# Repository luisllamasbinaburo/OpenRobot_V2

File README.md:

# OpenRobot v2

OpenRobot v2 is an Open Hardware PCB based on Arduino Nano, especially designed for teaching technology

Once assembled, you can use make multiple projects and robots without welding, just adding or removing components in the dupont headers.

OpenRobot v2 is based on a modular design. Just select your main MCU module (Arduino Nano, ESP32, M5Stack...), and the module your project needs (Motors, GPIOs expansion...). Check the Wiki for information about each module.

## What can I make with OpenRobot v2?
Almost any DIY project you can ever imagine! 

Some of them,
- DC Motors Robot, like obstacle avoider (ultrasonic or Sharp), line follower, self-balancing bot...
- Servo Motor Robot, like 2-DOF Tower, 6-DOF Arms...
- Mosfet output for high current proyects (LED, electromagnets, water pumps)
- Bluetooth projects (HC-05/HC-06), like Android or PC communication, beacons...
- WiFi projects (ESP01), like controlling from Web, MQTT datalogger...
- Temperature, pressure, humidity weather station with BME280
- Any other project, thanks to the multiple available outputs!

## Modules
More info about each module in Wiki

#### PowerSource
- DC Converter ([Wiki link](https://github.com/luisllamasbinaburo/OpenRobot_V2/wiki/Module_PowerSource))

#### MCUs
- Arduino Nano ([Wiki link](https://github.com/luisllamasbinaburo/OpenRobot_V2/wiki/Module_MCU_ArduinoNano))
- ESP32 Embed ([Wiki link](https://github.com/luisllamasbinaburo/OpenRobot_V2/wiki/Module_MCU_ESP32Embed))
- M5StickC / M5Stack Atom ([Wiki link](https://github.com/luisllamasbinaburo/OpenRobot_V2/wiki/Module_MCU_M5Stack))

#### Motors
- DC Motors ([Wiki link](https://github.com/luisllamasbinaburo/OpenRobot_V2/wiki/Module_Motor_DC))
- Steppers ([Wiki link](https://github.com/luisllamasbinaburo/OpenRobot_V2/wiki/Module_Motor_Stepper))
- I2C Servos ([Wiki link](https://github.com/luisllamasbinaburo/OpenRobot_V2/wiki/Module_I2C_Servo))

#### Expansions
- I2C GPIO ([Wiki link](https://github.com/luisllamasbinaburo/OpenRobot_V2/wiki/Module_I2C_GPIO))
- I2C TOF ([Wiki link](https://github.com/luisllamasbinaburo/OpenRobot_V2/wiki/Module_I2C_TOF))
- Mosfet ([Wiki link](https://github.com/luisllamasbinaburo/OpenRobot_V2/wiki/Module_Expansion_Mosfet))

## TODO:
- Improve documentation
- Improve code source / utilities (libraries, examples...)

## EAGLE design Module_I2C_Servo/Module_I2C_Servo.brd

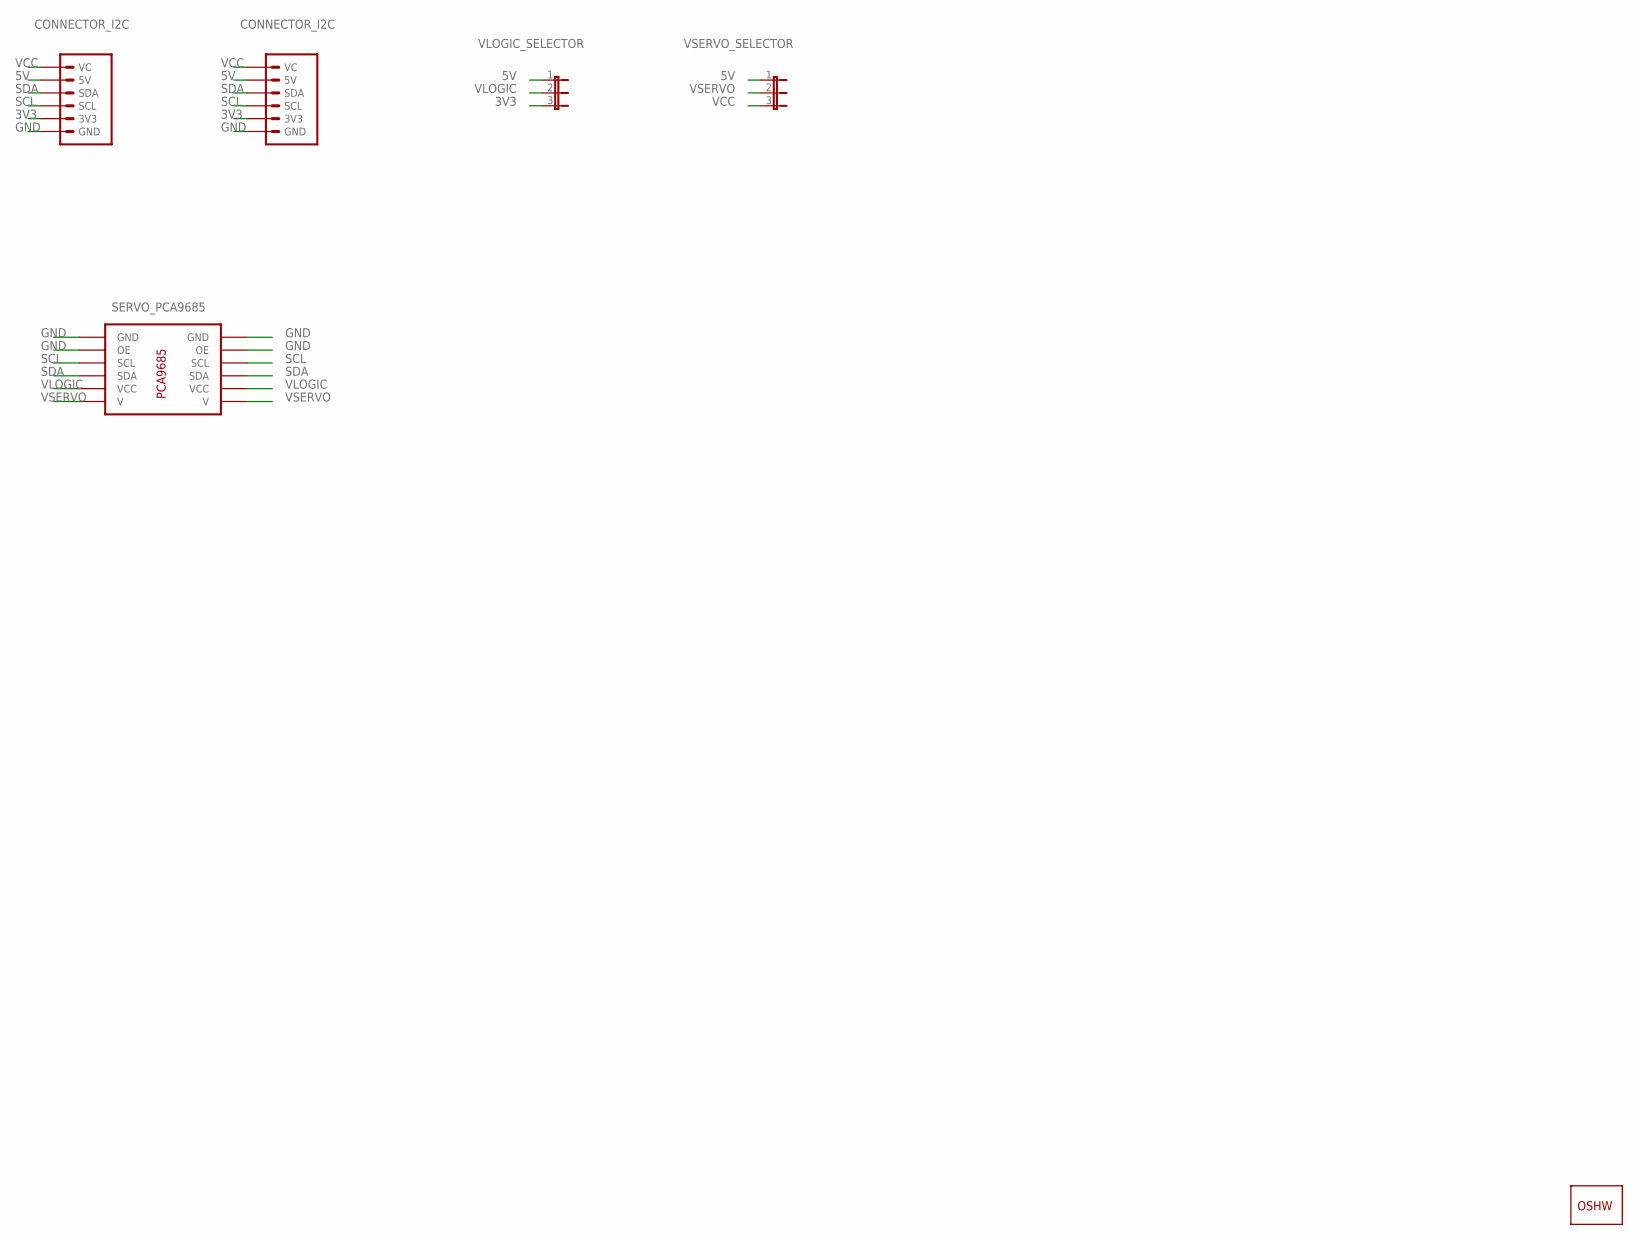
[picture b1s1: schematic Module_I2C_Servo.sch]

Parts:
GOLD_ORB_SM1: OSHWLOGO_GOLD_ORB_MED; OSHW1
U$2: SERVO_PCA9685
U$3, U$4: CONNECTOR_I2C
VLOGIC_SELECTOR: JUMPER_3
VSERVO_SELECTOR: JUMPER_3

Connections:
3V3: U$3.3V3, U$4.3V3, VLOGIC_SELECTOR.3
5V: U$3.5V, U$4.5V, VLOGIC_SELECTOR.1, VSERVO_SELECTOR.1
GND: U$2.GND@0 (GND), U$2.GND@1 (GND), U$2.OE@0 (OE), U$2.OE@1 (OE), U$3.GND, U$4.GND
SCL: U$2.SCL@0 (SCL), U$2.SCL@1 (SCL), U$3.SCL, U$4.SCL
SDA: U$2.SDA@0 (SDA), U$2.SDA@1 (SDA), U$3.SDA, U$4.SDA
VCC: U$3.VC, U$4.VC, VSERVO_SELECTOR.3
VLOGIC: U$2.VCC@0 (VCC), U$2.VCC@1 (VCC), VLOGIC_SELECTOR.2
VSERVO: U$2.VSERVO@0 (V), U$2.VSERVO@1 (V), VSERVO_SELECTOR.2

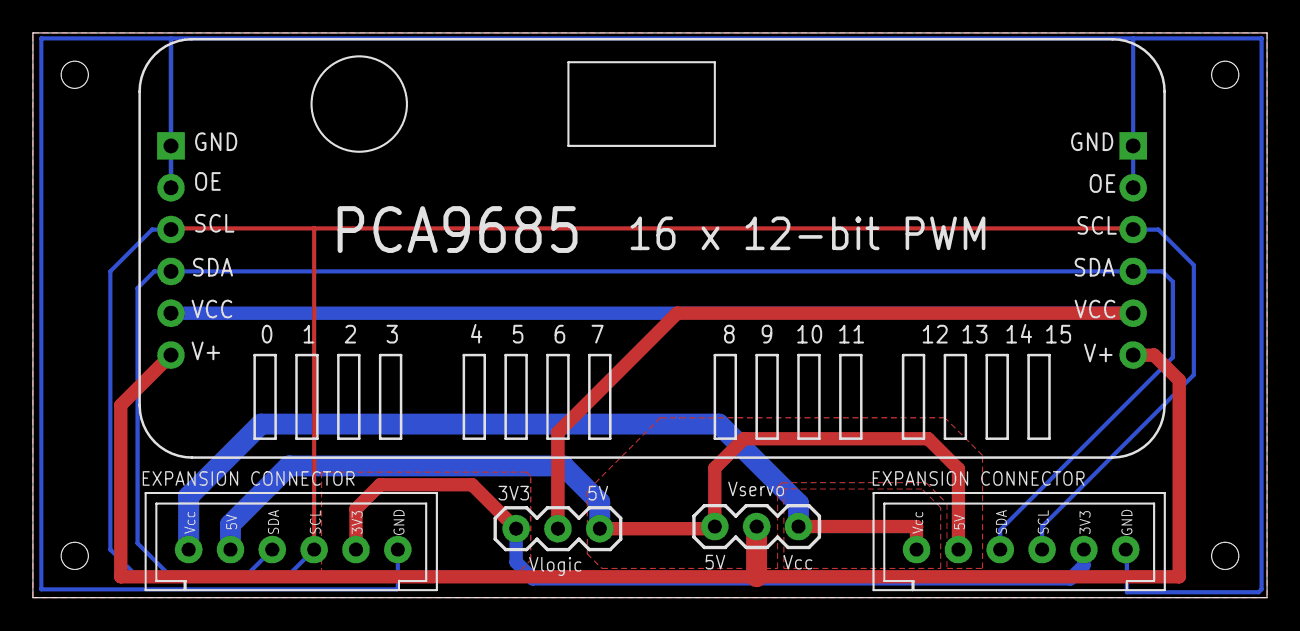
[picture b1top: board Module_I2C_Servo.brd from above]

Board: 2 copper layers, 74.9 x 34.3 mm, 6 parts (1 on the bottom side), 8 nets.

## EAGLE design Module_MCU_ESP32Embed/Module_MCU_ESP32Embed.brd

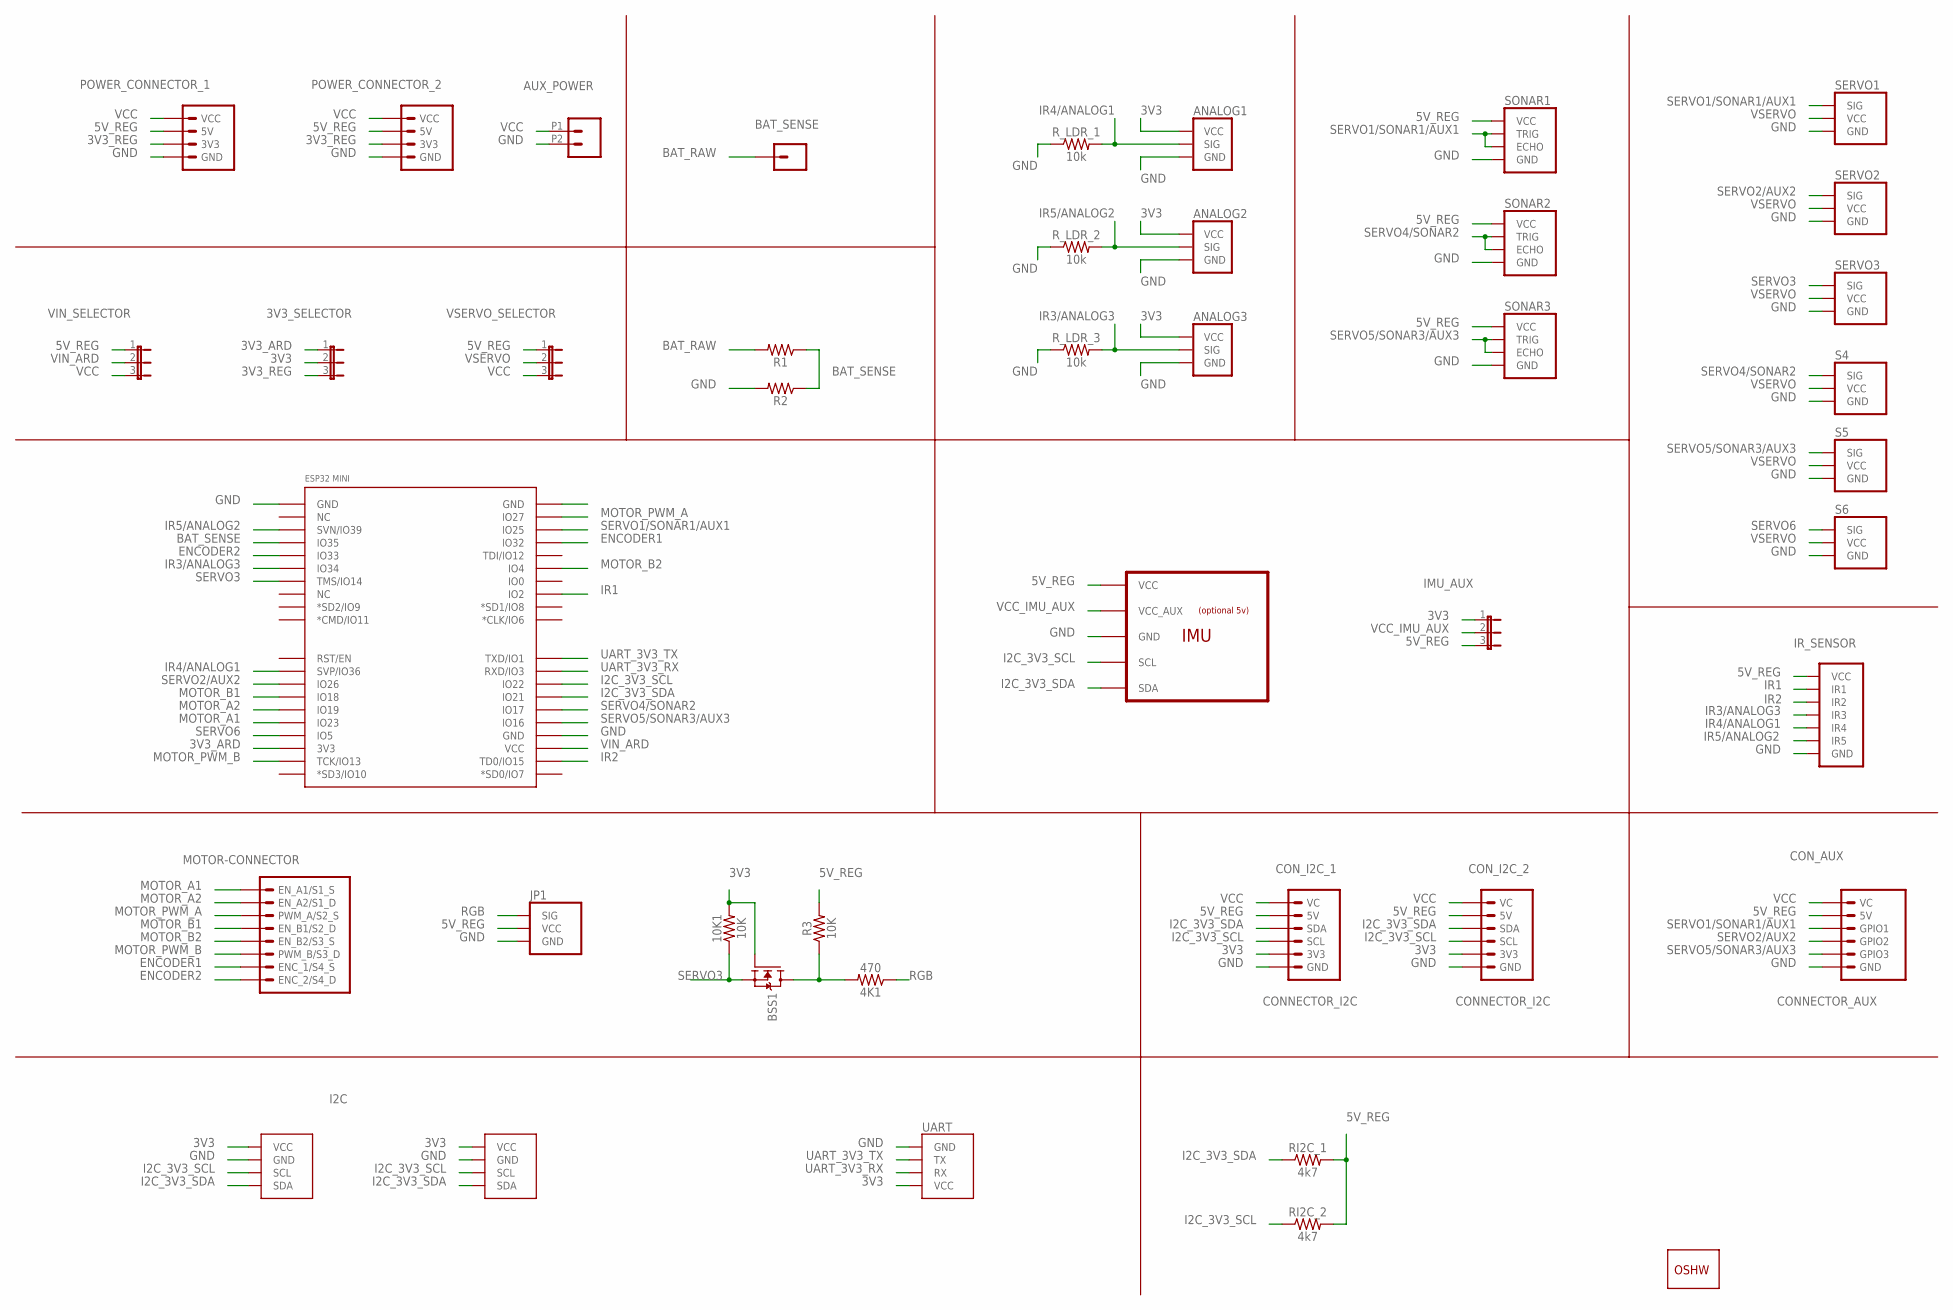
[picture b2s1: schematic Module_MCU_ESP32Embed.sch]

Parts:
3V3_SELECTOR: JUMPER_3
4K1: 470; 0805
10K1: 10K; 0805
ANALOG1, ANALOG2, ANALOG3: LDR/OCT; LDR
AUX_POWER: CONN_022.54MM_SCREWTERM; 1X02_2.54_SCREWTERM
BAT_SENSE: CONN_01; 1X01
BSS1: MOSFET-N-SOT23; SOT23
CON_AUX: CONNECTOR_AUX
CON_I2C_1, CON_I2C_2: CONNECTOR_I2C
GOLD_ORB_SM1: OSHWLOGO_GOLD_ORB_MED; OSHW1
I2C_1: I2C; I2C_VCC_GND_SCL_SDA
I2C_2: GENERIC_I2CVCC_GND_SCL_SDA; I2C_VCC_GND_SCL_SDA
IMU_AUX: JUMPER_3
IR_SENSOR: IR-5/OCT; IR-5
JP1: SERVOSERVO; SERVO
MOTOR_CONNECTOR: MOTOR-CONNECTOR
POWER_CONNECTOR_1, POWER_CONNECTOR_2: POWER-CONNECTOR
R1, R2: 1206
R3: 10K; 0805
RI2C_1, RI2C_2: 4k7; 1206
R_LDR_1, R_LDR_2, R_LDR_3: 10k; 1206
S4, S5, S6: SERVOSERVO; SERVO
SERVO1, SERVO2, SERVO3: SERVOSERVO; SERVO
SONAR1, SONAR2, SONAR3: ULTRASONIC/OCT; ULTRASONIC
U1: IMU_6/9/10DOFMPU6050; IMU_6/9/10DOF
U$5: ESP32-WEMOS
UART: UART; GENERIC_UART
VIN_SELECTOR: JUMPER_3
VSERVO_SELECTOR: JUMPER_3

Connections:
3V3: 3V3_SELECTOR.2, 10K1.2, ANALOG1.VCC, ANALOG2.VCC, ANALOG3.VCC, BSS1.1 (G), CON_I2C_1.3V3, CON_I2C_2.3V3, I2C_1.VCC, I2C_2.VCC, IMU_AUX.1, UART.VCC
3V3_ARD: 3V3_SELECTOR.1, U$5.3V3
3V3_REG: 3V3_SELECTOR.3, POWER_CONNECTOR_1.3V3, POWER_CONNECTOR_2.3V3
5V_REG: CON_AUX.5V, CON_I2C_1.5V, CON_I2C_2.5V, IMU_AUX.3, IR_SENSOR.VCC, JP1.VCC, POWER_CONNECTOR_1.5V, POWER_CONNECTOR_2.5V, R3.2, RI2C_1.2, RI2C_2.2, SONAR1.VCC, SONAR2.VCC, SONAR3.VCC, U1.VCC, VIN_SELECTOR.1, VSERVO_SELECTOR.1
BAT_RAW: BAT_SENSE.1, R1.2
BAT_SENSE: R1.1, R2.1, U$5.IO35
ENCODER1: MOTOR_CONNECTOR.ENC_1/S4_S, U$5.IO32
ENCODER2: MOTOR_CONNECTOR.ENC_2/S4_D, U$5.IO33
GND: ANALOG1.GND, ANALOG2.GND, ANALOG3.GND, AUX_POWER.P2 (2), CON_AUX.GND, CON_I2C_1.GND, CON_I2C_2.GND, I2C_1.GND, I2C_2.GND, IR_SENSOR.GND, JP1.GND, POWER_CONNECTOR_1.GND, POWER_CONNECTOR_2.GND, R2.2, R_LDR_1.1, R_LDR_2.1, R_LDR_3.1, S4.GND, S5.GND, S6.GND, SERVO1.GND, SERVO2.GND, SERVO3.GND, SONAR1.GND, SONAR2.GND, SONAR3.GND, U1.GND, U$5.GND@1 (GND), U$5.GND@3 (GND), UART.GND
I2C_3V3_SCL: CON_I2C_1.SCL, CON_I2C_2.SCL, I2C_1.SCL, I2C_2.SCL, RI2C_2.1, U1.SCL, U$5.IO22
I2C_3V3_SDA: CON_I2C_1.SDA, CON_I2C_2.SDA, I2C_1.SDA, I2C_2.SDA, RI2C_1.1, U1.SDA, U$5.IO21
IR1: IR_SENSOR.1 (IR1), U$5.IO2
IR2: IR_SENSOR.2 (IR2), U$5.TD0/IO15
IR3/ANALOG3: ANALOG3.SIG, IR_SENSOR.3 (IR3), R_LDR_3.2, U$5.IO34
IR4/ANALOG1: ANALOG1.SIG, IR_SENSOR.4 (IR4), R_LDR_1.2, U$5.SVP/IO36
IR5/ANALOG2: ANALOG2.SIG, IR_SENSOR.5 (IR5), R_LDR_2.2, U$5.SVN/IO39
MOTOR_A1: MOTOR_CONNECTOR.EN_A1/S1_S, U$5.IO23
MOTOR_A2: MOTOR_CONNECTOR.EN_A2/S1_D, U$5.IO19
MOTOR_B1: MOTOR_CONNECTOR.EN_B1/S2_D, U$5.IO18
MOTOR_B2: MOTOR_CONNECTOR.EN_B2/S3_S, U$5.IO4
MOTOR_PWM_A: MOTOR_CONNECTOR.PWM_A/S2_S, U$5.IO27
MOTOR_PWM_B: MOTOR_CONNECTOR.PWM_B/S3_D, U$5.TCK/IO13
unnamed: 4K1.2, BSS1.3 (D), R3.1
RGB: 4K1.1, JP1.SIG
SERVO1/SONAR1/AUX1: CON_AUX.GPIO1, SERVO1.SIG, SONAR1.ECHO, SONAR1.TRIG, U$5.IO25
SERVO2/AUX2: CON_AUX.GPIO2, SERVO2.SIG, U$5.IO26
SERVO3: 10K1.1, BSS1.2 (S), SERVO3.SIG, U$5.TMS/IO14
SERVO4/SONAR2: S4.SIG, SONAR2.ECHO, SONAR2.TRIG, U$5.IO17
SERVO5/SONAR3/AUX3: CON_AUX.GPIO3, S5.SIG, SONAR3.ECHO, SONAR3.TRIG, U$5.IO16
SERVO6: S6.SIG, U$5.IO5
UART_3V3_RX: U$5.RXD/IO3, UART.RX
UART_3V3_TX: U$5.TXD/IO1, UART.TX
VCC: AUX_POWER.P1 (1), CON_AUX.VC, CON_I2C_1.VC, CON_I2C_2.VC, POWER_CONNECTOR_1.VCC, POWER_CONNECTOR_2.VCC, VIN_SELECTOR.3, VSERVO_SELECTOR.3
VCC_IMU_AUX: IMU_AUX.2, U1.VCC_AUX
VIN_ARD: U$5.VCC, VIN_SELECTOR.2
VSERVO: S4.VCC, S5.VCC, S6.VCC, SERVO1.VCC, SERVO2.VCC, SERVO3.VCC, VSERVO_SELECTOR.2

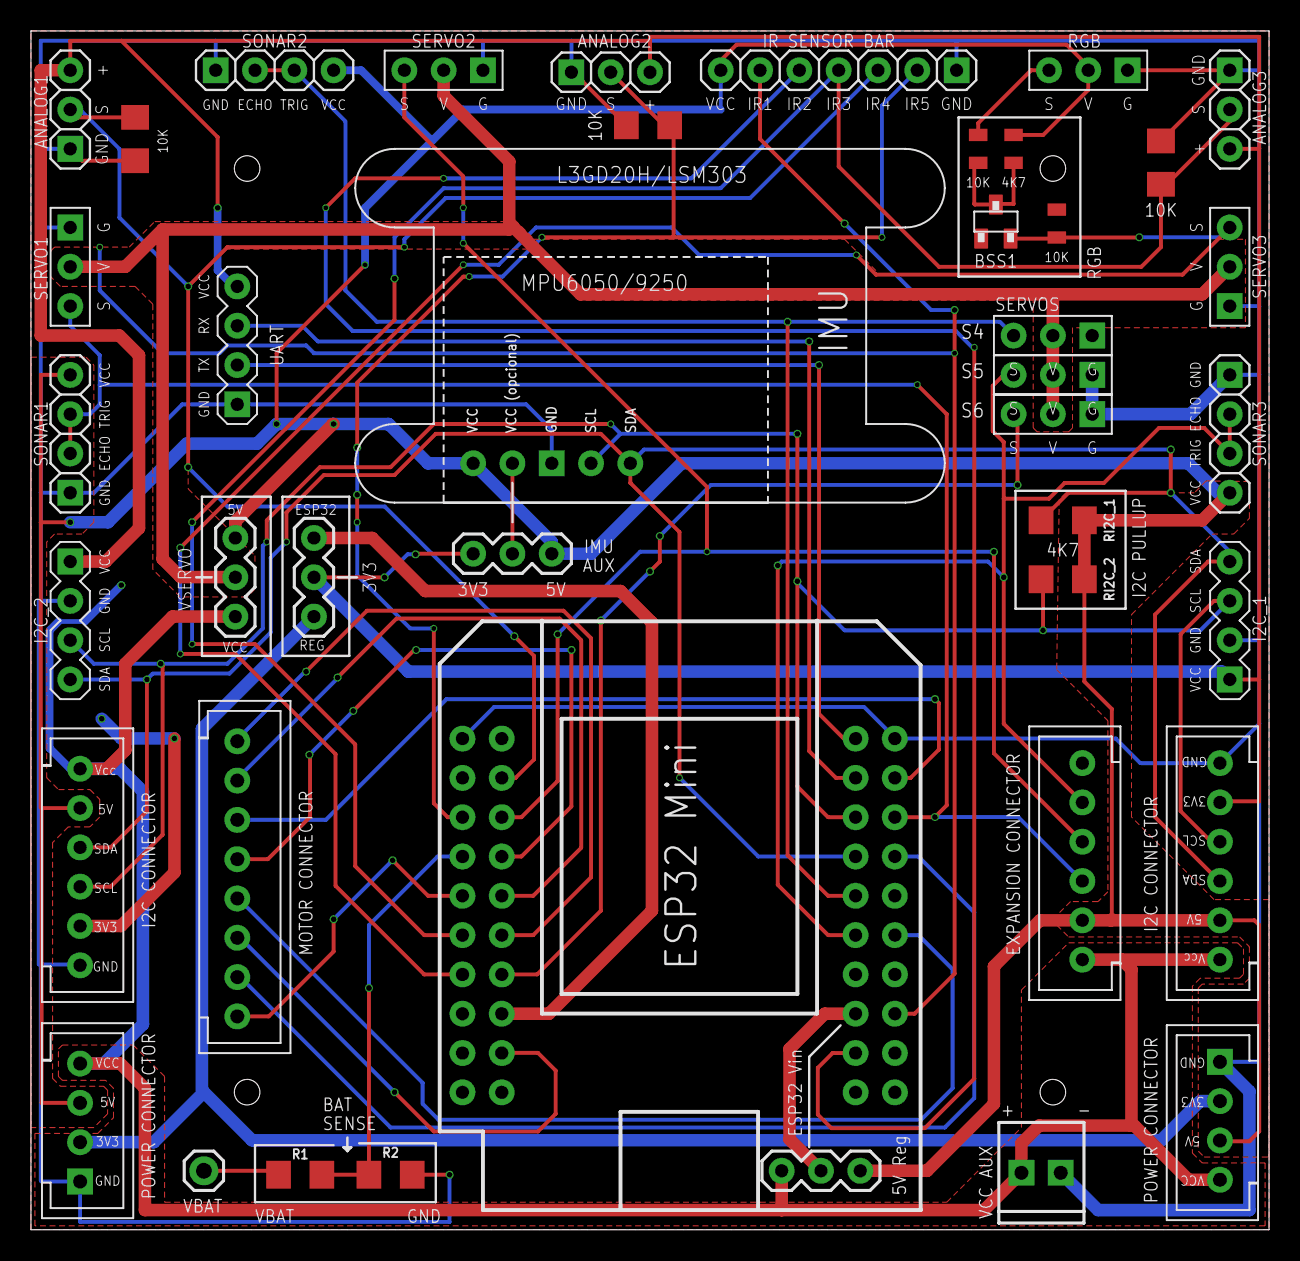
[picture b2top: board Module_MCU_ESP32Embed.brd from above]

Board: 2 copper layers, 80.0 x 77.5 mm, 43 parts (1 on the bottom side), 36 nets.

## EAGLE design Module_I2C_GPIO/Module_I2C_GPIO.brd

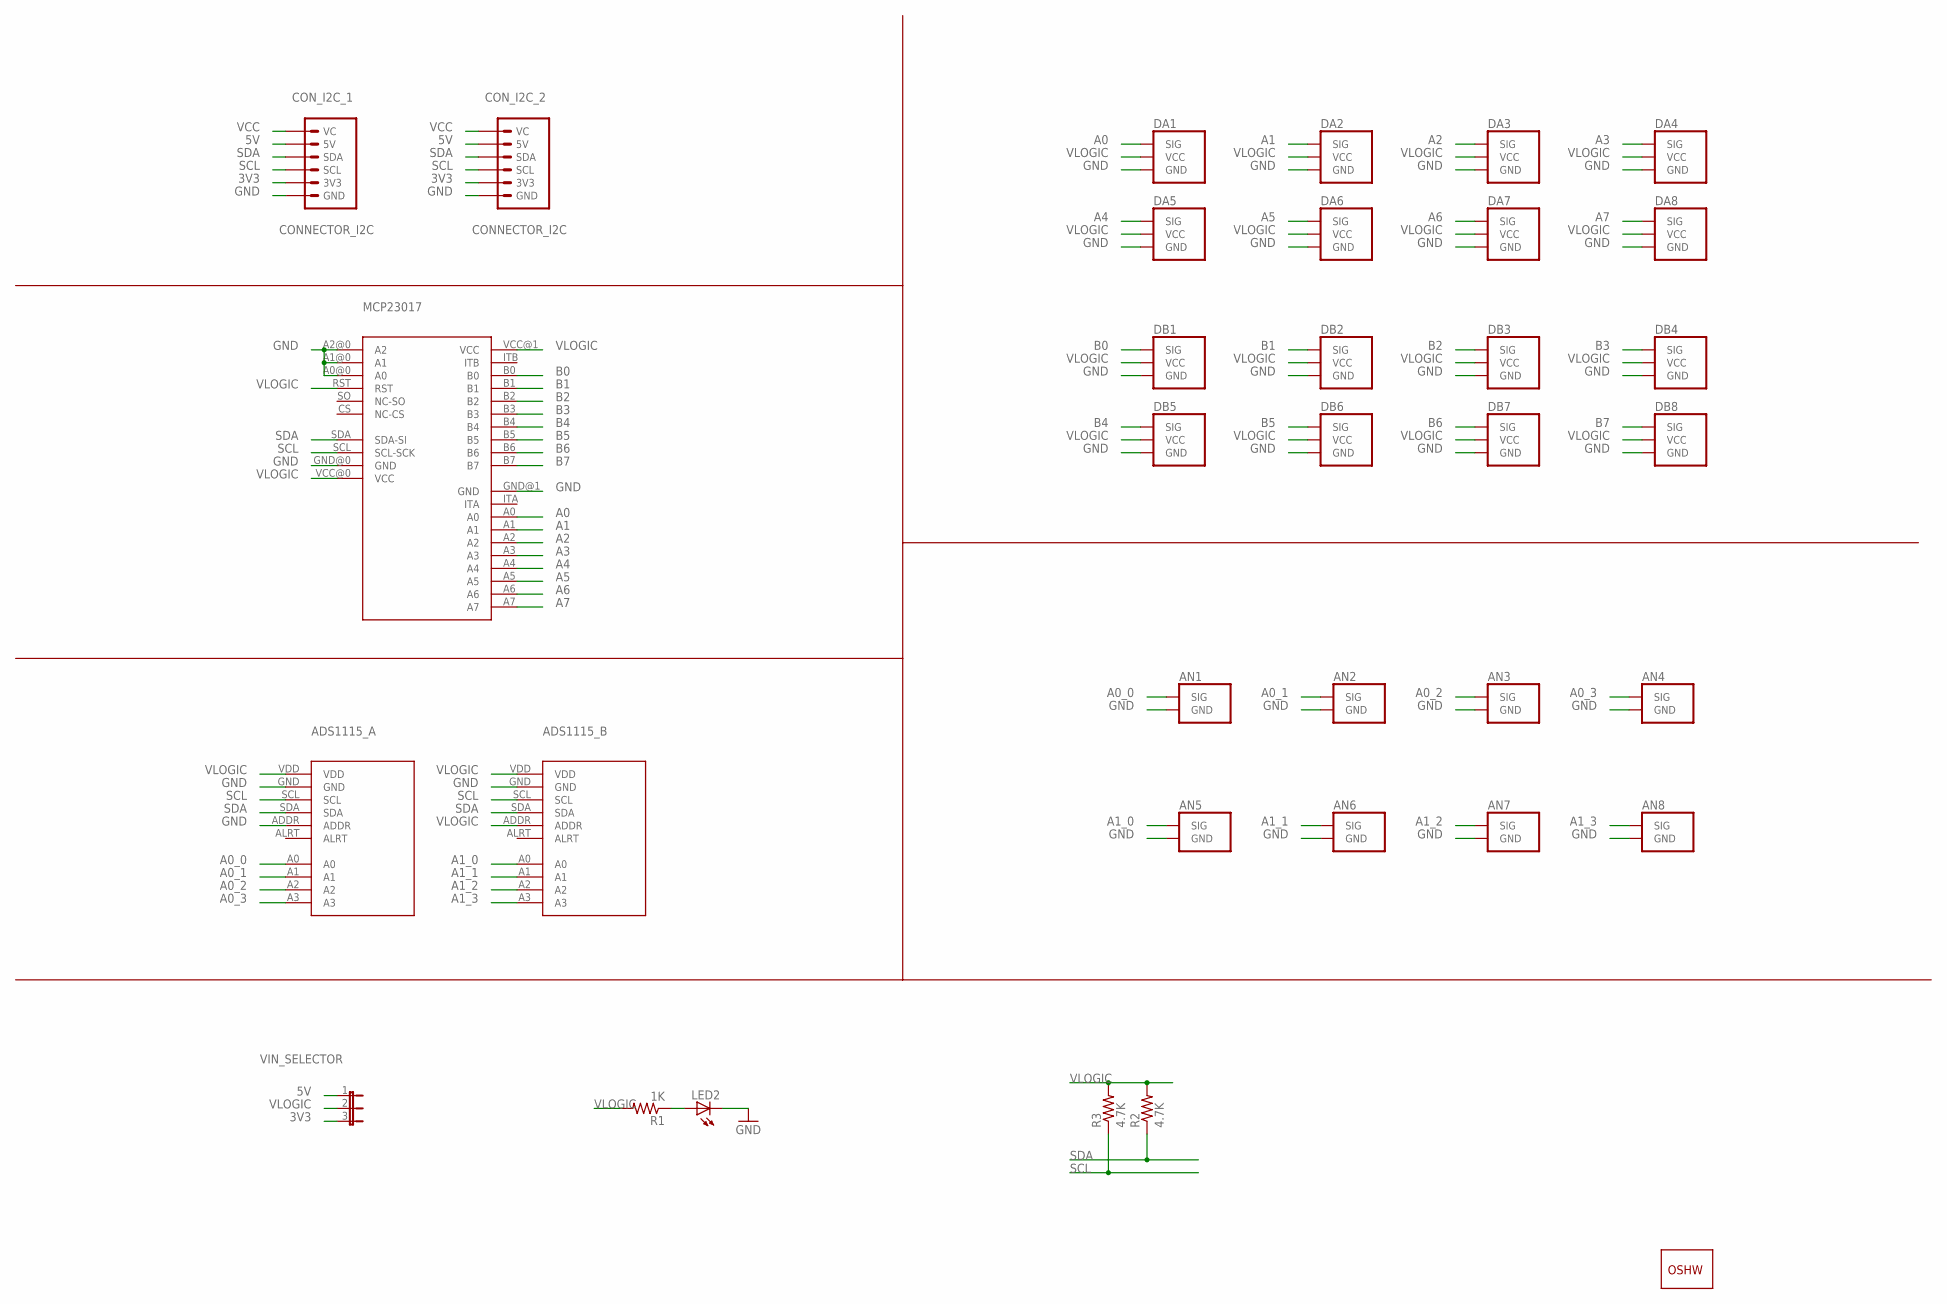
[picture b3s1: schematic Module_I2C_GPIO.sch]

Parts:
ADS1115_A, ADS1115_B: ADC-4CH-ADS1115
AN1, AN2, AN3, AN4, AN5, AN6, AN7, AN8: SERVO_2
CON_I2C_1, CON_I2C_2: CONNECTOR_I2C
DA1, DA2, DA3, DA4, DA5, DA6, DA7, DA8: SERVOSERVO; SERVO
DB1, DB2, DB3, DB4, DB5, DB6, DB7, DB8: SERVOSERVO; SERVO
GOLD_ORB_SM1: OSHWLOGO_GOLD_ORB_MED; OSHW1
LED2: LEDCHIP-LED0805; CHIP-LED0805
MCP23017: GPIO-I2C-MCP23017
R1: 1K; R0805
R2, R3: 4.7K; R0805
VIN_SELECTOR: JUMPER_3

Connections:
3V3: CON_I2C_1.3V3, CON_I2C_2.3V3, VIN_SELECTOR.3
5V: CON_I2C_1.5V, CON_I2C_2.5V, VIN_SELECTOR.1
A0: DA1.SIG, MCP23017.A0
A0_0: ADS1115_A.A0, AN1.SIG
A0_1: ADS1115_A.A1, AN2.SIG
A0_2: ADS1115_A.A2, AN3.SIG
A0_3: ADS1115_A.A3, AN4.SIG
A1: DA2.SIG, MCP23017.A1
A1_0: ADS1115_B.A0, AN5.SIG
A1_1: ADS1115_B.A1, AN6.SIG
A1_2: ADS1115_B.A2, AN7.SIG
A1_3: ADS1115_B.A3, AN8.SIG
A2: DA3.SIG, MCP23017.A2
A3: DA4.SIG, MCP23017.A3
A4: DA5.SIG, MCP23017.A4
A5: DA6.SIG, MCP23017.A5
A6: DA7.SIG, MCP23017.A6
A7: DA8.SIG, MCP23017.A7
B0: DB1.SIG, MCP23017.B0
B1: DB2.SIG, MCP23017.B1
B2: DB3.SIG, MCP23017.B2
B3: DB4.SIG, MCP23017.B3
B4: DB5.SIG, MCP23017.B4
B5: DB6.SIG, MCP23017.B5
B6: DB7.SIG, MCP23017.B6
B7: DB8.SIG, MCP23017.B7
GND: ADS1115_A.ADDR, ADS1115_A.GND, ADS1115_B.GND, AN1.GND, AN2.GND, AN3.GND, AN4.GND, AN5.GND, AN6.GND, AN7.GND, AN8.GND, CON_I2C_1.GND, CON_I2C_2.GND, DA1.GND, DA2.GND, DA3.GND, DA4.GND, DA5.GND, DA6.GND, DA7.GND, DA8.GND, DB1.GND, DB2.GND, DB3.GND, DB4.GND, DB5.GND, DB6.GND, DB7.GND, DB8.GND, LED2.C, MCP23017.A0@0 (A0), MCP23017.A1@0 (A1), MCP23017.A2@0 (A2), MCP23017.GND@0 (GND), MCP23017.GND@1 (GND)
unnamed: LED2.A, R1.1
SCL: ADS1115_A.SCL, ADS1115_B.SCL, CON_I2C_1.SCL, CON_I2C_2.SCL, MCP23017.SCL (SCL-SCK), R3.1
SDA: ADS1115_A.SDA, ADS1115_B.SDA, CON_I2C_1.SDA, CON_I2C_2.SDA, MCP23017.SDA (SDA-SI), R2.1
VCC: CON_I2C_1.VC, CON_I2C_2.VC
VLOGIC: ADS1115_A.VDD, ADS1115_B.ADDR, ADS1115_B.VDD, DA1.VCC, DA2.VCC, DA3.VCC, DA4.VCC, DA5.VCC, DA6.VCC, DA7.VCC, DA8.VCC, DB1.VCC, DB2.VCC, DB3.VCC, DB4.VCC, DB5.VCC, DB6.VCC, DB7.VCC, DB8.VCC, MCP23017.RST, MCP23017.VCC@0 (VCC), MCP23017.VCC@1 (VCC), R1.2, R2.2, R3.2, VIN_SELECTOR.2

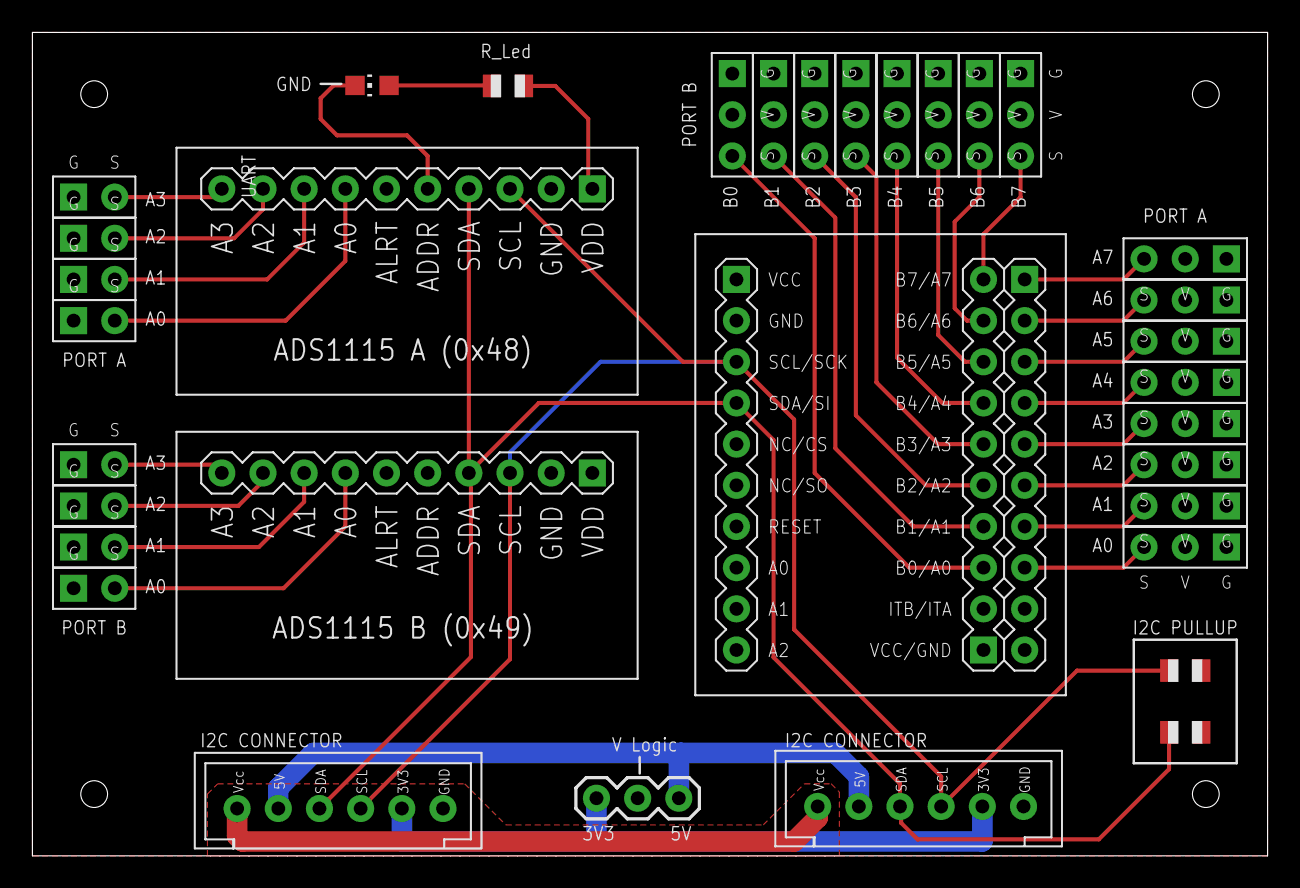
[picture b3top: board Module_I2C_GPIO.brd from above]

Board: 2 copper layers, 76.2 x 50.8 mm, 35 parts (1 on the bottom side), 32 nets.

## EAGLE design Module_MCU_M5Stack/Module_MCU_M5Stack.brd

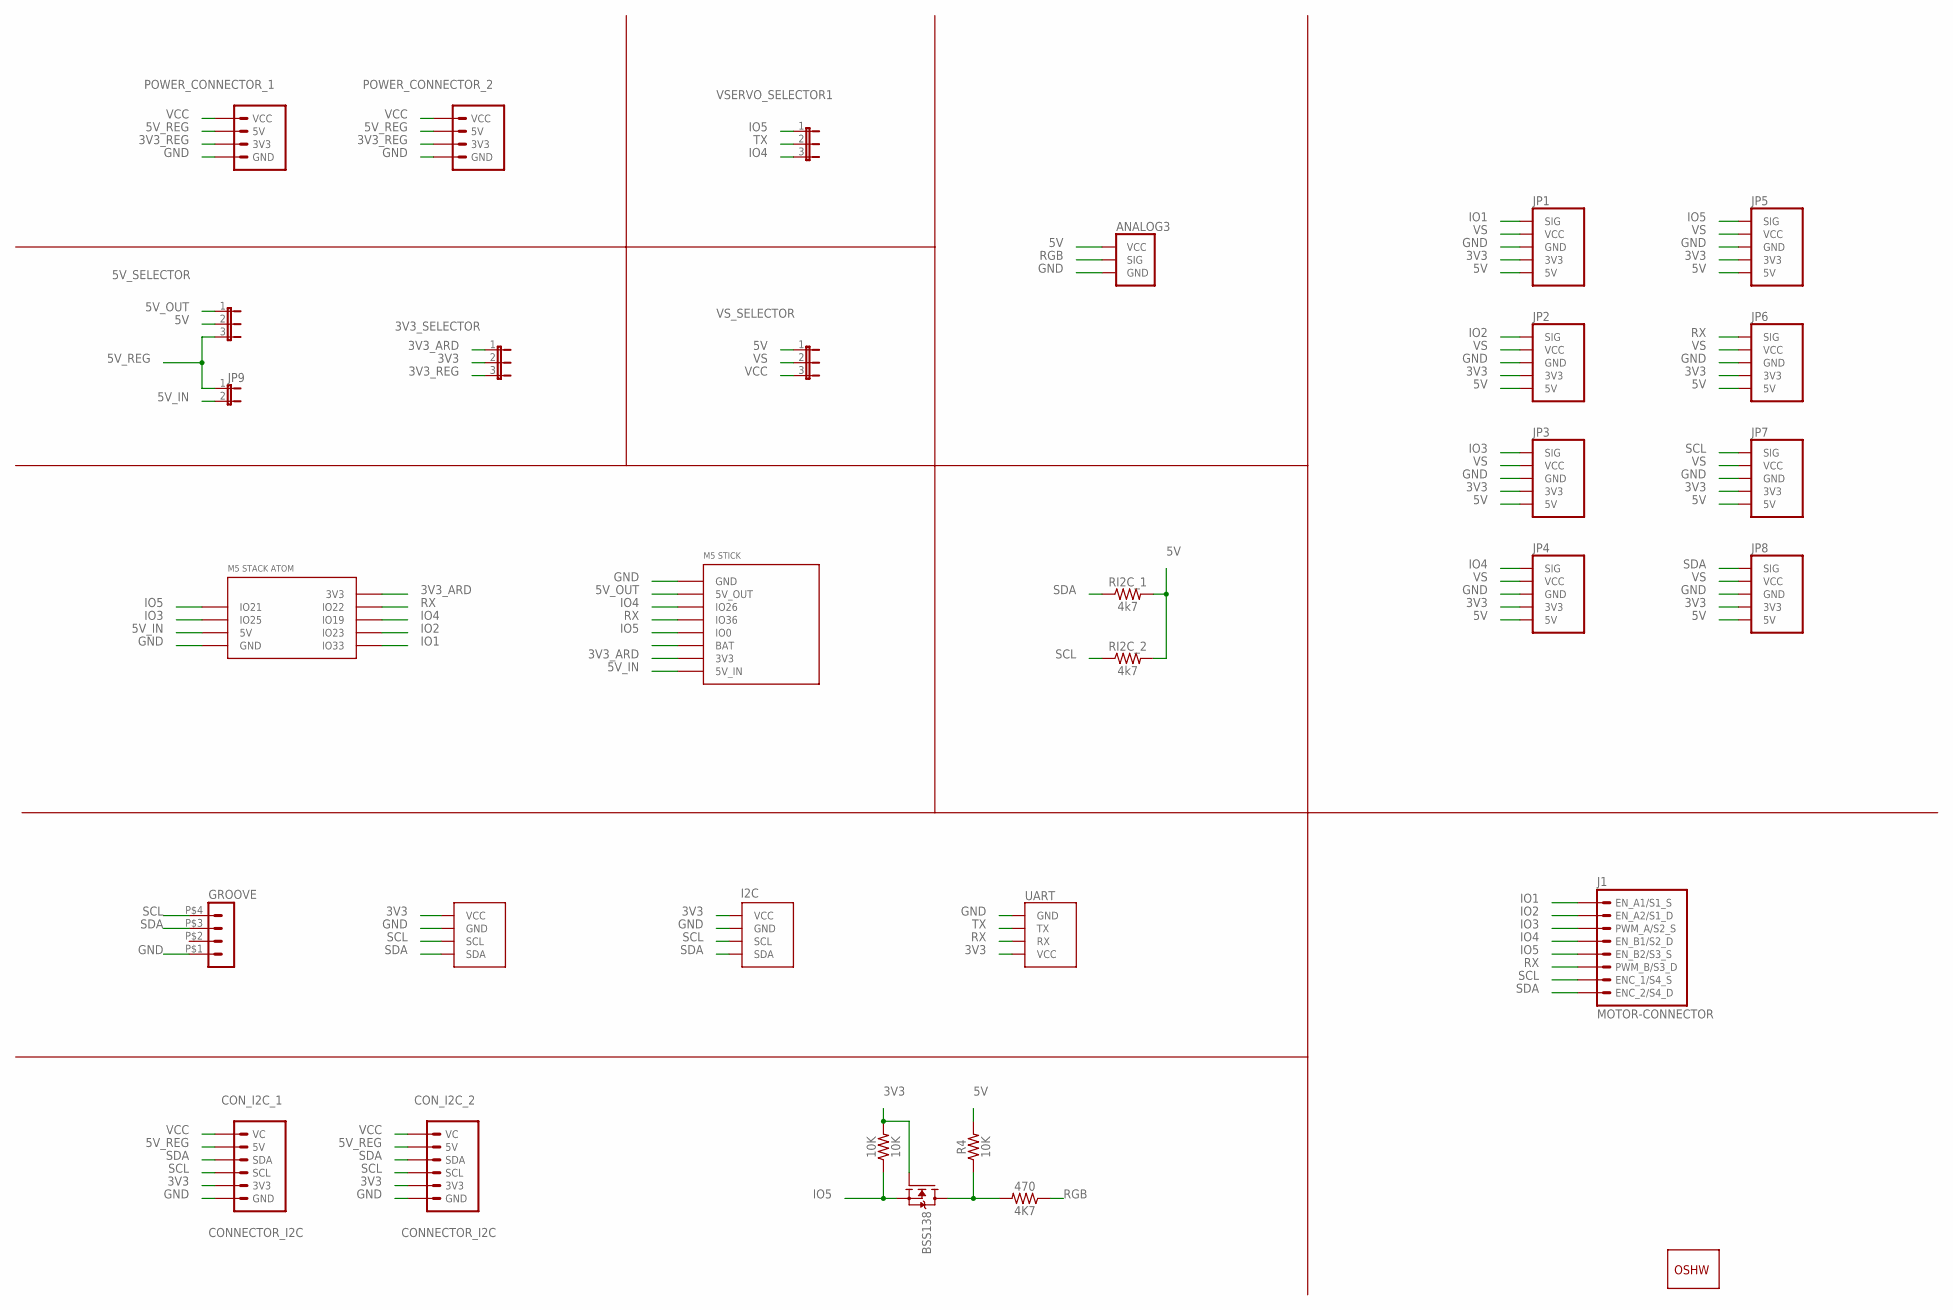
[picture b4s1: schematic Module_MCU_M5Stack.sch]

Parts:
3V3_SELECTOR, 5V_SELECTOR: JUMPER_3
4K7: 470; 0805
10K: 10K; 0805
ANALOG3: LDR/OCT; LDR
BSS138: MOSFET-N-SOT23; SOT23
CON_I2C_1, CON_I2C_2: CONNECTOR_I2C
GOLD_ORB_SM1: OSHWLOGO_GOLD_ORB_MED; OSHW1
GROOVE: GROOVE
I2C_1: I2C; I2C_VCC_GND_SCL_SDA
I2C_2: GENERIC_I2CVCC_GND_SCL_SDA; I2C_VCC_GND_SCL_SDA
J1: MOTOR-CONNECTOR
JP1, JP2, JP3, JP4, JP5, JP6, JP7, JP8: SERVO_5
JP9: JUMPER_2PTH; JUMPER_2
POWER_CONNECTOR_1, POWER_CONNECTOR_2: POWER-CONNECTOR
R4: 10K; 0805
RI2C_1, RI2C_2: 4k7; 1206
U$1: M5-STACK-ATOM
U$2: M5-STICK
UART: UART; GENERIC_UART
VSERVO_SELECTOR1: JUMPER_3
VS_SELECTOR: JUMPER_3

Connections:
3V3: 3V3_SELECTOR.2, 10K.2, BSS138.1 (G), CON_I2C_1.3V3, CON_I2C_2.3V3, I2C_1.VCC, I2C_2.VCC, JP1.3V3, JP2.3V3, JP3.3V3, JP4.3V3, JP5.3V3, JP6.3V3, JP7.3V3, JP8.3V3, UART.VCC
3V3_ARD: 3V3_SELECTOR.1, U$1.3V3, U$2.3V3
3V3_REG: 3V3_SELECTOR.3, POWER_CONNECTOR_1.3V3, POWER_CONNECTOR_2.3V3
5V: 5V_SELECTOR.2, ANALOG3.VCC, JP1.5V, JP2.5V, JP3.5V, JP4.5V, JP5.5V, JP6.5V, JP7.5V, JP8.5V, R4.2, RI2C_1.2, RI2C_2.2, VS_SELECTOR.1
5V_IN: JP9.2, U$1.5V, U$2.5V_IN
5V_OUT: 5V_SELECTOR.1, U$2.5V_OUT
5V_REG: 5V_SELECTOR.3, CON_I2C_1.5V, CON_I2C_2.5V, JP9.1, POWER_CONNECTOR_1.5V, POWER_CONNECTOR_2.5V
GND: ANALOG3.GND, CON_I2C_1.GND, CON_I2C_2.GND, GROOVE.P$1 (1), I2C_1.GND, I2C_2.GND, JP1.GND, JP2.GND, JP3.GND, JP4.GND, JP5.GND, JP6.GND, JP7.GND, JP8.GND, POWER_CONNECTOR_1.GND, POWER_CONNECTOR_2.GND, U$1.GND, U$2.GND, UART.GND
IO1: J1.EN_A1/S1_S, JP1.SIG, U$1.IO33
IO2: J1.EN_A2/S1_D, JP2.SIG, U$1.IO23
IO3: J1.PWM_A/S2_S, JP3.SIG, U$1.IO25
IO4: J1.EN_B1/S2_D, JP4.SIG, U$1.IO19, U$2.IO26, VSERVO_SELECTOR1.3
IO5: 10K.1, BSS138.2 (S), J1.EN_B2/S3_S, JP5.SIG, U$1.IO21, U$2.IO0, VSERVO_SELECTOR1.1
unnamed: 4K7.2, BSS138.3 (D), R4.1
RGB: 4K7.1, ANALOG3.SIG
RX: J1.PWM_B/S3_D, JP6.SIG, U$1.IO22, U$2.IO36, UART.RX
SCL: CON_I2C_1.SCL, CON_I2C_2.SCL, GROOVE.P$4 (4), I2C_1.SCL, I2C_2.SCL, J1.ENC_1/S4_S, JP7.SIG, RI2C_2.1
SDA: CON_I2C_1.SDA, CON_I2C_2.SDA, GROOVE.P$3 (3), I2C_1.SDA, I2C_2.SDA, J1.ENC_2/S4_D, JP8.SIG, RI2C_1.1
TX: UART.TX, VSERVO_SELECTOR1.2
VCC: CON_I2C_1.VC, CON_I2C_2.VC, POWER_CONNECTOR_1.VCC, POWER_CONNECTOR_2.VCC, VS_SELECTOR.3
VS: JP1.VCC, JP2.VCC, JP3.VCC, JP4.VCC, JP5.VCC, JP6.VCC, JP7.VCC, JP8.VCC, VS_SELECTOR.2

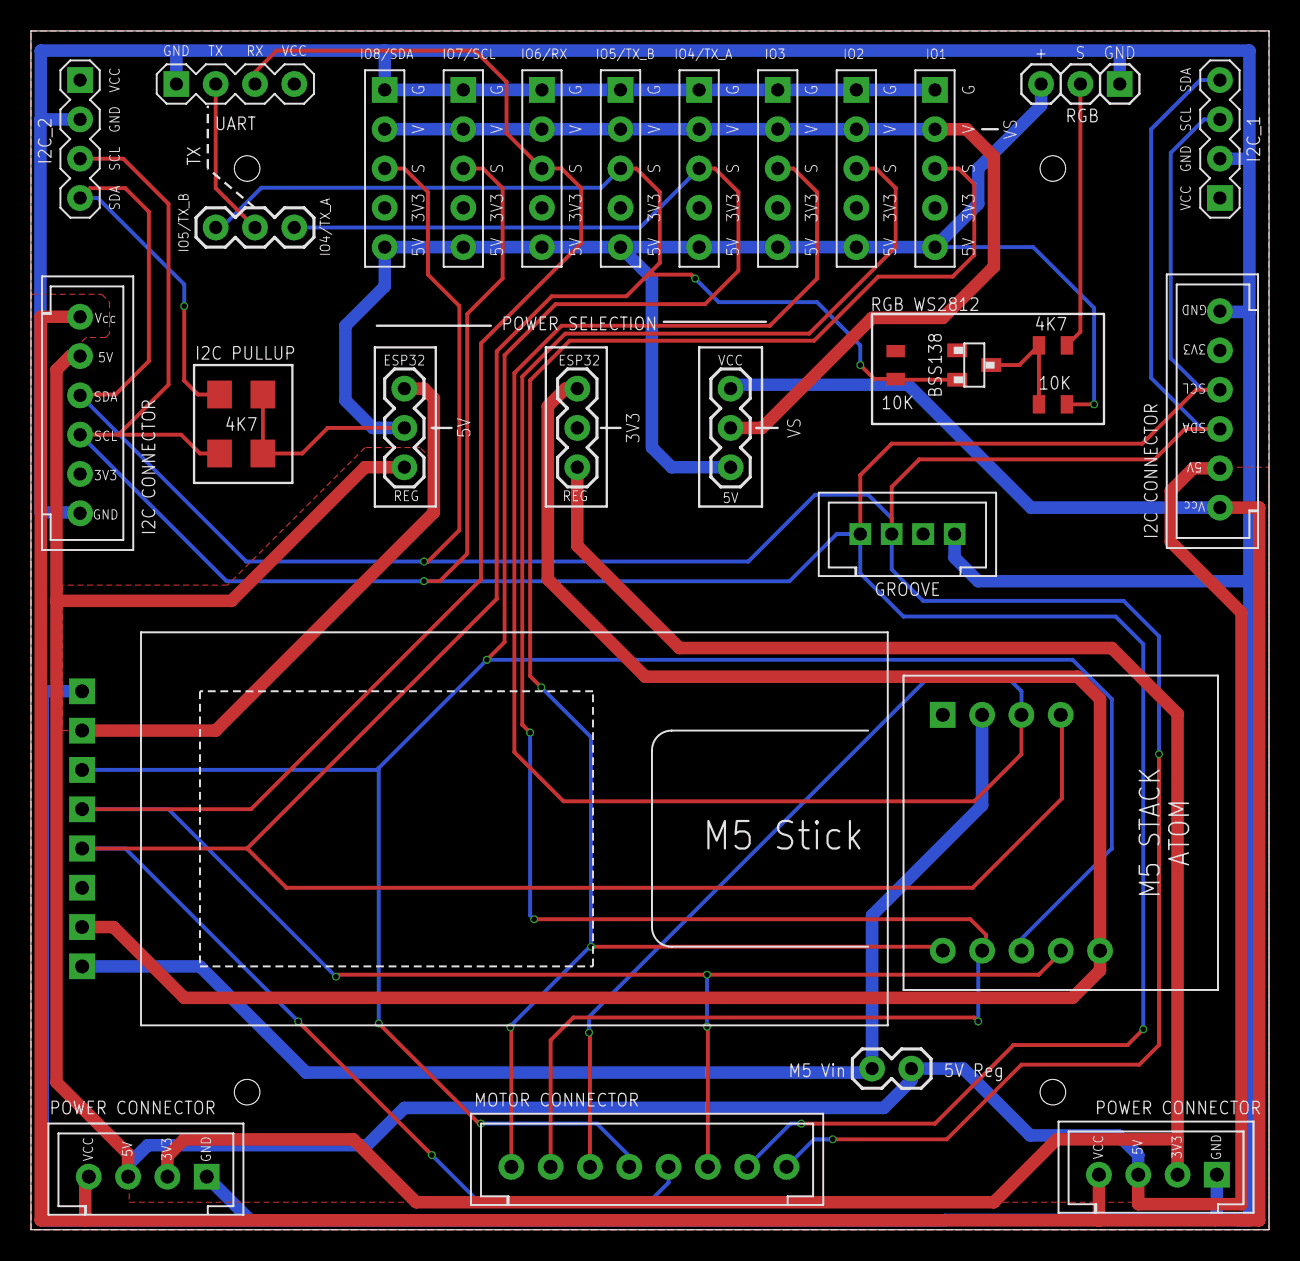
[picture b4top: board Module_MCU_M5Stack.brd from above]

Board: 2 copper layers, 80.0 x 77.5 mm, 32 parts (1 on the bottom side), 21 nets.

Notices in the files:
Module_Motor_Stepper/Module_Motor_Stepper.brd:
GPL3
parts and their libraries:
SparkFun-DiscreteSemi: Licensing: Creative Commons ShareAlike 4.0 International - https://creativecommons.org/licenses/by-sa/4.0
